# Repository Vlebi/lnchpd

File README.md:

A compact, custom-designed USB-MIDI controller built for live DJ performance, sample triggering, and live looping. Powered by a Raspberry Pi Pico (RP2040) and custom-routed PCBs, running native MicroPython.

Features:

USB-MIDI: Works out of the box with any DAW without requiring custom drivers (i think so).

Multi-Page: 4 dynamic performance pads that switch their uses by paging, providing lots of features from a compact size.

4-Track Looper: Dedicated loop page where each pad handles its own loop track (Record, Playback, Stop, and Long-Press Erase). Supports cross-page recording.

Hardware Design: Built on a 2-layer 57mm x 62.1mm PCB with a copper ground pour (might need to let this one go for budget porpuses) and TACTR-12x12x7.5 tactile switches.

Button Layout and Controls:

Pads 1 to 4 (GPIO 0 to 3): Dynamic performance pads. Function changes based on the active page:

Page 0 (Drums): General MIDI drum map (Kick, Snare, Closed Hi-Hat, Clap).

Page 1 (samples): Sample triggers.

Page 2 (4-Track Looper): Control independent loop tracks 1 to 4.

Page 3 (Synth / Piano): Monophonic and polyphonic melodic scale leads.

Button 5 (GPIO 4): Page Switcher (Cycles through Drums, SFX, Looper, and Synth).

Button 6 (GPIO 5): Global Looper Command (Long press to wipe all tracks globally).

Button 7 (GPIO 6): FX Control 1 (Sends Control Change CC 16).

Button 8 (GPIO 7): FX Control 2 (Sends Control Change CC 17).

BOM:

Microcontroller: Raspberry Pi Pico

Switches: 8x TACTR-12x12x7.5 THT tactile microswitches

PCB: 2-layer FR4 board (57mm x 62.1mm) with a common ground rail layout

Getting Started and Firmware Installation:

Flash MicroPython.

Connect your Pico via USB.

Copy the main.py script and save it directly onto the Pico as main.py so it boots automatically.

Open your music software's MIDI settings, enable the Pico as an active input device, and map it.

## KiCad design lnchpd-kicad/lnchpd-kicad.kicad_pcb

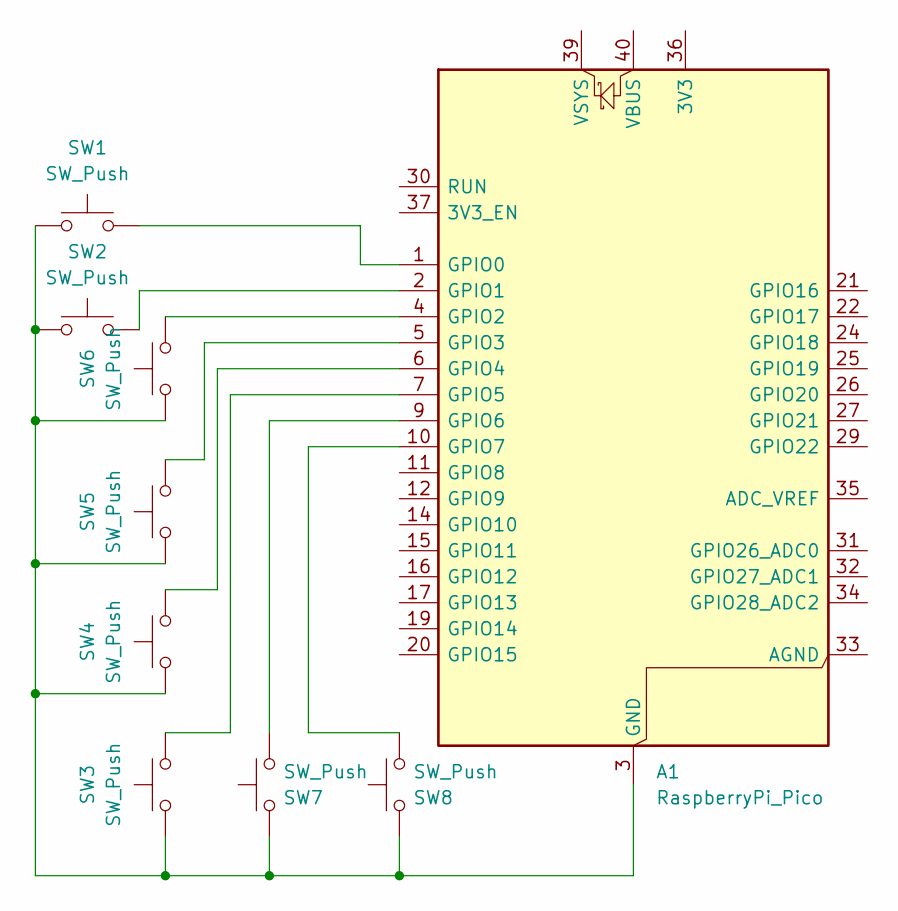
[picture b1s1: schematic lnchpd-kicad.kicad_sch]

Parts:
A1: RaspberryPi_Pico; RaspberryPi_Pico_Common_Unspecified
SW1, SW2, SW3, SW4, SW5, SW6, SW7, SW8: SW_Push; SW_NKK_GW12LJP

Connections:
unnamed: A1.3 (GND), A1.8 (GND), A1.13 (GND), A1.18 (GND), A1.23 (GND), A1.28 (GND), A1.38 (GND), SW1.1, SW2.1, SW3.1, SW4.1, SW5.1, SW6.1, SW7.2, SW8.2
unnamed: A1.1 (GPIO0), SW1.2
unnamed: A1.2 (GPIO1), SW2.2
unnamed: A1.4 (GPIO2), SW6.2
unnamed: A1.5 (GPIO3), SW5.2
unnamed: A1.6 (GPIO4), SW4.2
unnamed: A1.7 (GPIO5), SW3.2
unnamed: A1.9 (GPIO6), SW7.1
unnamed: A1.10 (GPIO7), SW8.1

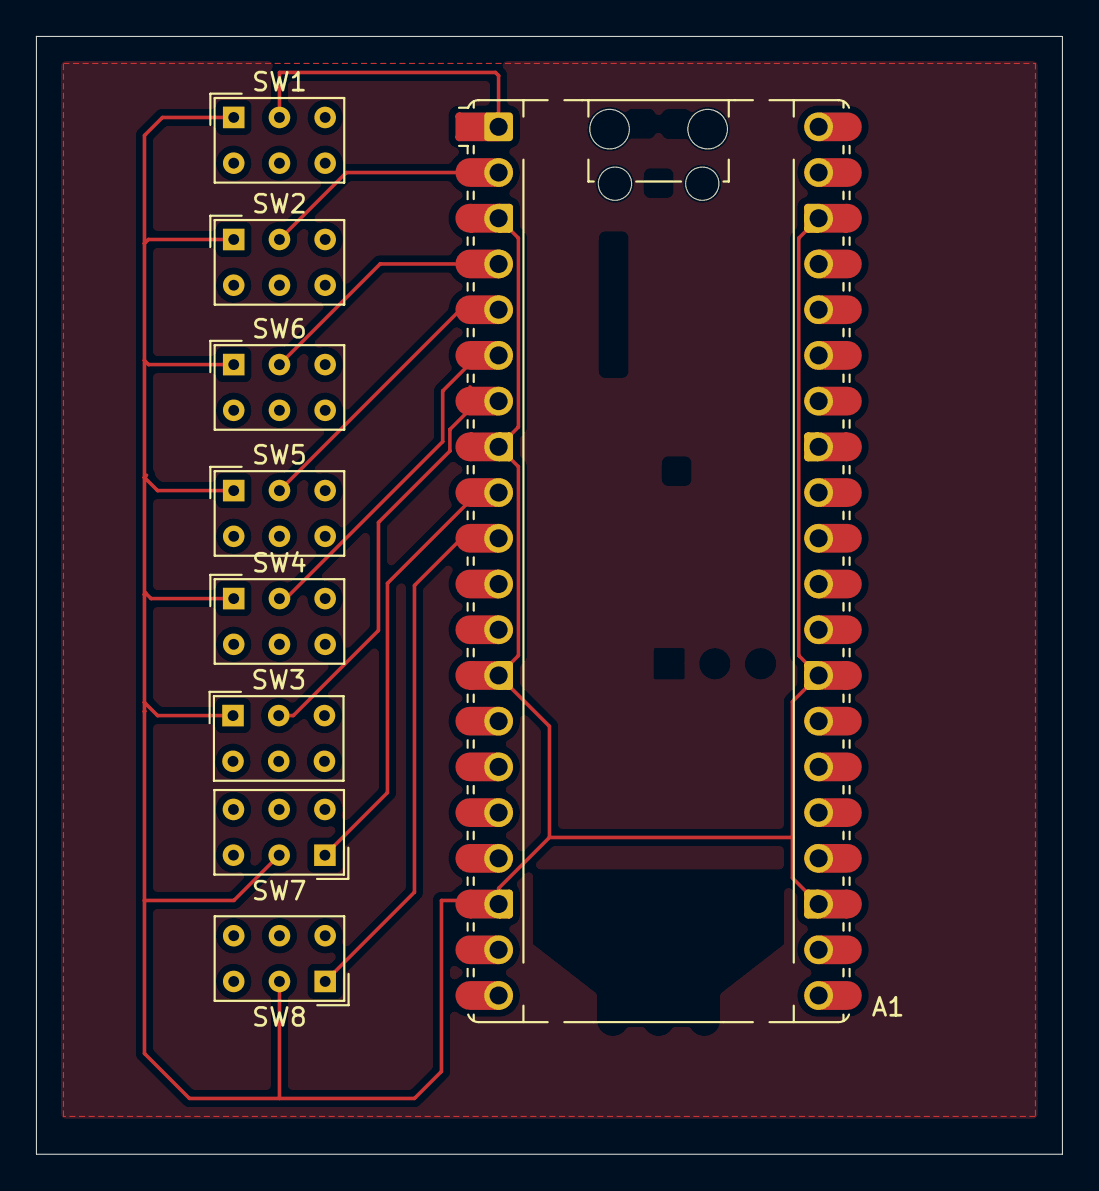
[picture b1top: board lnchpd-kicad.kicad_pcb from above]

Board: 2 copper layers, 57.0 x 62.1 mm, 9 parts (0 on the bottom side), 9 nets.
